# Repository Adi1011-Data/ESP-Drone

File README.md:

# ESP-Drone (XIAO ESP32-C3)

A 1S brushed micro quad. The Seeed XIAO ESP32-C3 is the flight controller. A custom ESC board holds the MPU6050 and four MOSFET motor channels. You fly from the ESP-Drone phone app over the XIAO’s Wi-Fi. This tree is [Circuit Digest ESP-Drone](https://github.com/Circuit-Digest/ESP-Drone) / Espressif ESP-Drone, retargeted from the ESP32-S3 to the ESP32-C3.

Read this page before soldering, installing tools, or flashing.

## What you are building

```text
1S LiPo  -->  ESC board  -->  four 720 coreless motors
                 |  MPU6050 (gyro + accel)
                 |  four AO3400A low-side FETs
                 |
           XIAO ESP32-C3  -->  Wi-Fi AP  -->  phone app (sticks)
                              HTTP :80     -->  laptop (PID page)
                              USB-C        -->  attitude viewer
```

The phone never closes the attitude loop. The chip reads the MPU6050, runs cascaded PID at 500 Hz, and mixes the four motors. If stick packets stop, throttle goes to zero.

This board has no barometer, magnetometer, or optical flow. Stabilize / manual flight only. Height-hold and position-hold need extra sensors that are not fitted.

## Simulation links

The local pages are served by this PC, not by the ESP. They open with the board off. From `simulation/`, start the server and leave that window open. Closing it stops port 8765, and the browser cannot open the sites.

```powershell
.\serve.ps1
```

| Tool | Local (ESP can be off) | On the drone Wi-Fi |
| --- | --- | --- |
| Landing page | http://127.0.0.1:8765/ | — |
| Attitude viewer | http://127.0.0.1:8765/viewer/ | USB or BLE from that page |
| PID tuner | http://127.0.0.1:8765/pid/ | http://192.168.43.42/ |

http://192.168.43.42/ is the ESP. It opens only when the board is on and the laptop has joined its Wi-Fi.

- **Attitude viewer:** props off. Close `idf.py monitor`. Chrome or Edge. Connect USB (or BLE) and tilt the board. The on-screen quad copies the MPU6050.
- **PID tuner:** phone stays on `ESP-DRONE_…` for sticks (UDP **2390**). Laptop joins the same AP. Open the PID link (HTTP **80**). Do not point a second CRTP client at 2390.

More detail: [simulation/README.md](simulation/README.md).

## Architecture

```text
Phone app  --UDP 2390 CRTP-->  Wi-Fi AP (192.168.43.42)
Laptop     --HTTP 80------->  same AP, PID dashboard
USB-C      --ATT,w,x,y,z-->  attitude viewer

Stick angles --> Angle PID --> desired rates --> Rate PID --> mixer --> MOT1..4
                 (outer)                        (inner, gyro)
```

| Piece | What it does |
| --- | --- |
| XIAO ESP32-C3 | Wi-Fi AP, USB Serial/JTAG, PID, PWM to the FETs |
| MPU6050 | Gyro and accelerometer on I2C `0x68` |
| AO3400A × 4 | One low-side switch per brushed motor |
| SS14 × 4 | Flyback diode on each motor |
| ESP-Drone 0.7.3 | Stick input over CRTP |
| PID page | Live Kp/Ki/Kd; Save writes NVS |

Factory PID: [Firmware/main/include/board/pid_config.h](Firmware/main/include/board/pid_config.h). Pins and Wi-Fi: [Firmware/main/include/board/drone_config.h](Firmware/main/include/board/drone_config.h).

Tune **Rate** (inner) until it is calm, then **Angle** (outer). Rate is “don’t wobble.” Angle is “follow the stick.”

## Downloads and tools (do this before flashing)

Work on Windows. Scripts and paths in this repo assume the tools live on **E:** under `Drone-ESC\downloads`. Anaconda Python must not be the `python` that ESP-IDF finds.

1. **ESP-IDF 5.0.7 offline installer** (~0.96 GB)  
   Put `esp-idf-tools-setup-offline-5.0.7.exe` in `downloads/`.  
   Get it from Espressif’s IDF installer releases: [idf-installer](https://github.com/espressif/idf-installer/releases) (offline 5.0.7).

2. **Install onto this drive** (not `C:\Espressif`):

   ```powershell
   cd E:\Drone-ESC\downloads
   .\install-esp-idf-5.0.7.ps1
   ```

   In the installer: keep PowerShell selected, select the **ESP32-C3** target. Tools land in `downloads\Espressif`. The IDF tree is `downloads\Espressif\frameworks\esp-idf-v5.0.7`. The Python venv is `downloads\Espressif\python_env\idf5.0_py3.11_env`.

3. **Phone app** — [ESP-Drone 0.7.3 for Android](https://www.pgyer.com/a27L). Do not change drone IP `192.168.43.42` or UDP port `2390`.

4. **Browser** — Chrome or Edge for the attitude viewer (Web Serial / Web Bluetooth).

5. **Python 3** — only needed for `simulation\serve.ps1` (`python -m http.server`). The IDF venv is enough if it is on PATH.

6. **KiCad 10** — only if you will edit the PCB.

You do not need Node, Docker, or a second copy of ESP-IDF.

## Build and flash

From the repo root, in an ESP-IDF 5.0.7 shell (see the installer notes above):

```powershell
cd Firmware
idf.py set-target esp32c3
idf.py build
```

The image is `Firmware\build\ESPDrone.bin`. `idf.py flash` does not work on this XIAO. Flash with esptool and `usb_reset`, as in [Firmware/FLASHING.md](Firmware/FLASHING.md). Unplug the battery if props are on.

## Bring-up order (props off)

1. 3.3 V present, XIAO seated the right way around.
2. Flash, then USB serial: MPU6050 OK, AP up.
3. Attitude viewer: tilt matches the on-screen quad. Invert an axis in the page if needed; flip `DRONE_GYRO_*_SIGN` / `DRONE_ACC_*_SIGN` in firmware if the board is mechanically reversed.
4. One motor at a time, no props: each corner spins the right way. Swap that motor’s two leads if it is backward. If a corner climbs in a hover, that mixer channel is wrong — see comments in `drone_config.h`.
5. Phone joins `ESP-DRONE_<MAC>`, password `12345678`, app Connect. Throttle at zero, then a blip. Killing the app or leaving Wi-Fi must stop the motors.
6. Props on only after that. First hover in a soft, open space.
7. PID: laptop on the same AP, open http://192.168.43.42/ . Tune Rate, then Angle. **Save** to keep the tune across reboot.

## Fly

1. Power the drone and wait until it is sitting level.
2. Phone: Wi-Fi `ESP-DRONE_<MAC>`, password `12345678`.
3. ESP-Drone app → Connect. Sticks go to `192.168.43.42:2390`.

SSID prefix and password are in `drone_config.h`. Do not change the IP or UDP port; the 0.7.3 app expects them.

## Repo map

| Path | Contents |
| --- | --- |
| [Firmware](Firmware) | ESP-IDF 5.0.7 app |
| [Firmware/FLASHING.md](Firmware/FLASHING.md) | How this XIAO is actually programmed |
| [simulation](simulation) | Attitude viewer and PID tuner |
| [hardware/PCB/ESC](hardware/PCB/ESC) | Schematic, PCB, Gerbers, BOM |

Upstream video: [youtu.be/V_mZsiZcy7s](https://youtu.be/V_mZsiZcy7s). This board is C3, not S3.

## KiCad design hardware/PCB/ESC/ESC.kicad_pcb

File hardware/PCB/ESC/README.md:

# ESC-ESP32C3

A small brushed-motor ESC and flight-controller board for a drone built around a Seeed Studio XIAO ESP32-C3. The XIAO is the flight controller. An MPU6050 on the board supplies the accelerometer and gyroscope. Four 720 coreless motors are switched by AO3400A MOSFETs. The drone is flown from the ESP-Drone phone app over the XIAO's Wi-Fi.

## Board

Motor side. The XIAO plugs into headers J1 and J3. M1–M4 are the motor pads.

Sensor side. U1 is the MPU6050. The battery connects at the BAT pads.

## Parts

| Part | Role |
| --- | --- |
| Seeed Studio XIAO ESP32-C3 | Flight controller. Plugs into J1 and J3. |
| MPU6050 (U1) | 6-axis gyro and accelerometer, I2C address 0x68 (AD0 held low). |
| 720 coreless motor × 4 | Brushed motors on M1, M2, M3, and M4. |
| AO3400A × 4 | Low-side MOSFET for each motor. |
| Schottky diode × 4 | Flyback diode across each motor (SOD-323). |
| ESP-Drone app | Phone app used to control the drone. |

## XIAO pins

Seat the XIAO with the USB end toward the 5V / D0 end of the headers (J3 pin 1 is 5V, J1 pin 1 is D0).

| XIAO pin | GPIO | Function |
| --- | --- | --- |
| D0 | GPIO2 | Motor 1 gate (MOT1) |
| D3 | GPIO5 | Motor 2 gate (MOT2) |
| D9 | GPIO9 | Motor 3 gate (MOT3) |
| D10 | GPIO10 | Motor 4 gate (MOT4) |
| D4 | GPIO6 | MPU6050 SDA |
| D5 | GPIO7 | MPU6050 SCL |
| D7 | GPIO20 | MPU6050 interrupt |
| D2 | GPIO4 | Battery voltage sense |
| 3V3 | — | Sensor and gate pull-ups |
| GND | — | Common ground |

D9 is a boot strap pin. Its gate pull-down must leave the pin high enough at reset for the XIAO to start normally. Holding D9 low during reset puts the module into download mode.

D6 (GPIO21) is left free. It is the serial transmit pin and toggles while the chip boots.

## Assembly

1. Solder the MPU6050, MOSFETs, diodes, and passives.
2. Plug the XIAO ESP32-C3 into J1 and J3. Do not reverse it: 5V and D0 share one end of the module.
3. Solder one 720 coreless motor to each of M1–M4. The motor positive lead goes to the BAT+ pad of that pair.
4. Connect the flight battery at the BAT pads.
5. Power the XIAO, join its Wi-Fi from the ESP-Drone app, and arm the motors only after the propellers are clear.

## Design files

Open `ESC.kicad_pro` in KiCad 10.

| Path | Contents |
| --- | --- |
| `ESC.kicad_sch` | Schematic |
| `ESC.kicad_pcb` | PCB layout |
| `libraries/` | XIAO ESP32-C3 and MPU6050 symbols and footprints |
| `GERBER/` | Fabrication Gerbers and drill files |
| `ESC-BOM.csv` | Bill of materials |
| `ESC-all-pos.csv` | Pick-and-place positions |
| `ESC-ESP32.step` | 3D model of the board |

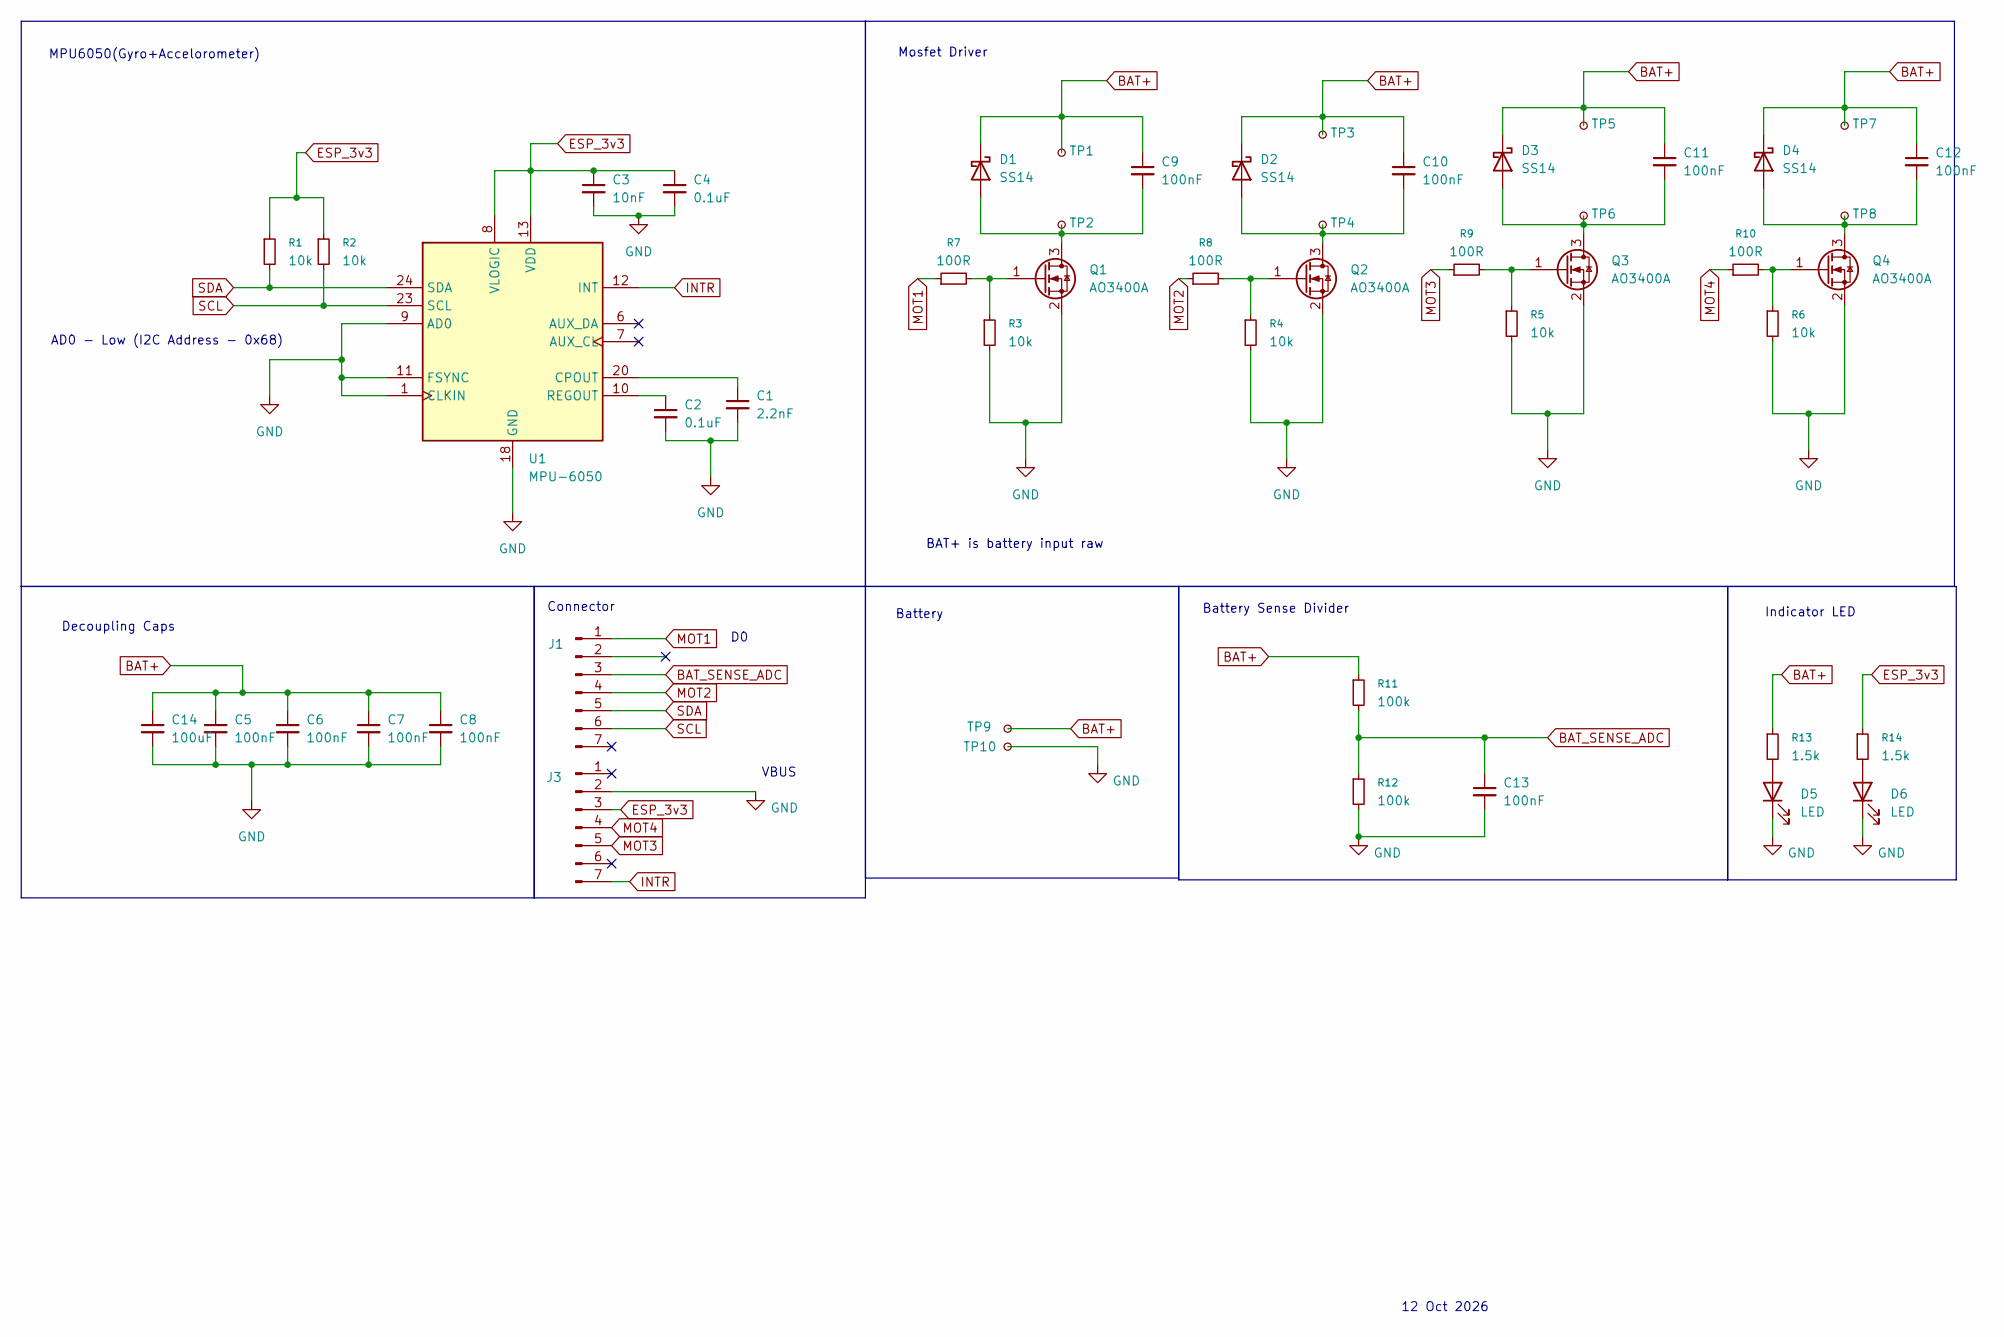
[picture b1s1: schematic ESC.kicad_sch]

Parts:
C1: 2.2nF; C_0402_1005Metric_Pad0.74x0.62mm_HandSolder
C2, C4: 0.1uF; C_0402_1005Metric_Pad0.74x0.62mm_HandSolder
C3: 10nF; C_0402_1005Metric_Pad0.74x0.62mm_HandSolder
C5, C6, C7, C8, C9, C10, C11, C12, C13: 100nF; C_0402_1005Metric_Pad0.74x0.62mm_HandSolder
C14: 100uF; C_0402_1005Metric_Pad0.74x0.62mm_HandSolder
D1, D2, D3, D4: SS14; D_SOD-323_HandSoldering
D5, D6: LED; LED_0402_1005Metric_Pad0.77x0.64mm_HandSolder
J1, J3: Conn_01x07_Pin; PinHeader_1x07_P2.54mm_Vertical
Q1, Q2, Q3, Q4: AO3400A; SOT-23
R1, R2, R3, R4, R5, R6: 10k; R_0402_1005Metric_Pad0.72x0.64mm_HandSolder
R7, R8, R9, R10: 100R; R_0402_1005Metric_Pad0.72x0.64mm_HandSolder
R11, R12: 100k; R_0402_1005Metric_Pad0.72x0.64mm_HandSolder
R13, R14: 1.5k; R_0402_1005Metric_Pad0.72x0.64mm_HandSolder
TP1, TP3, TP5, TP7, TP9: TestPoint_Small; TestPoint_Pad_1.0x1.0mm
TP2, TP4, TP6, TP8, TP10: TestPoint_Small; TestPoint_Pad_D1.0mm
U1: MPU-6050; InvenSense_QFN-24_4x4mm_P0.5mm

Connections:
BAT+: C5.1, C6.1, C7.1, C8.1, C9.1, C10.1, C11.1, C12.1, C14.1, D1.1 (K), D2.1 (K), D3.1 (K), D4.1 (K), R11.1, R13.1, TP1.1 (1_1), TP3.1 (1_1), TP5.1 (1_1), TP7.1 (1_1), TP9.1 (1_1)
BAT_SENSE_ADC: C13.1, J1.3, R11.2, R12.1
ESP_3v3: C3.1, C4.1, J3.3, R1.1, R2.1, R14.1, U1.8 (VLOGIC), U1.13 (VDD)
GND: C1.2, C2.2, C3.2, C4.2, C5.2, C6.2, C7.2, C8.2, C13.2, C14.2, D5.1 (K), D6.1 (K), J3.2, Q1.2 (S), Q2.2 (S), Q3.2 (S), Q4.2 (S), R3.2, R4.2, R5.2, R6.2, R12.2, TP10.1 (1_1), U1.1 (CLKIN), U1.9 (AD0), U1.11 (FSYNC), U1.18 (GND)
INTR: J3.7, U1.12 (INT)
MOT1: J1.1, R7.1
MOT2: J1.4, R8.1
MOT3: J3.5, R9.1
MOT4: J3.4, R10.1
unnamed: C9.2, D1.2 (A), Q1.3 (D), TP2.1 (1_1)
unnamed: C10.2, D2.2 (A), Q2.3 (D), TP4.1 (1_1)
unnamed: C11.2, D3.2 (A), Q3.3 (D), TP6.1 (1_1)
unnamed: C12.2, D4.2 (A), Q4.3 (D), TP8.1 (1_1)
unnamed: D5.2 (A), R13.2
unnamed: D6.2 (A), R14.2
unnamed: Q1.1 (G), R3.1, R7.2
unnamed: Q2.1 (G), R4.1, R8.2
unnamed: Q3.1 (G), R5.1, R9.2
unnamed: Q4.1 (G), R6.1, R10.2
unnamed: C1.1, U1.20 (CPOUT)
unnamed: C2.1, U1.10 (REGOUT)
SCL: J1.6, R2.2, U1.23 (SCL)
SDA: J1.5, R1.2, U1.24 (SDA)

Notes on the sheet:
BAT+ is battery input raw
Battery Sense Divider
12 Oct 2026
Decoupling Caps
Indicator LED
MPU6050(Gyro+Accelorometer)
Mosfet Driver
Battery
AD0 - Low (I2C Address - 0x68)
Connector
VBUS

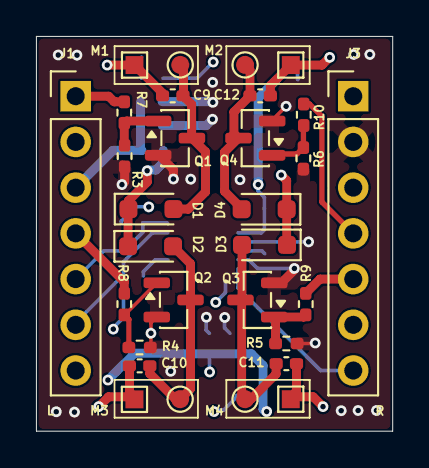
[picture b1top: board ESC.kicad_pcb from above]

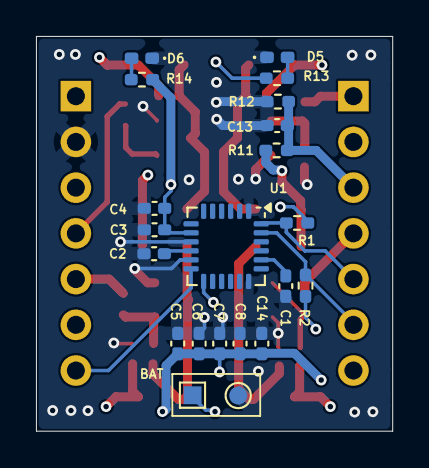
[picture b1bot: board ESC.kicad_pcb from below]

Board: 4 copper layers, 19.8 x 21.9 mm, 51 parts (21 on the bottom side), 23 nets.

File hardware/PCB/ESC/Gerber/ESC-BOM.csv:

"Id";"Designator";"Footprint";"Quantity";"Designation";"Supplier and ref";
1;"C1";"C_0402_1005Metric_Pad0.74x0.62mm_HandSolder";1;"2.2nF";;;
2;"C2, C4";"C_0402_1005Metric_Pad0.74x0.62mm_HandSolder";2;"0.1uF";;;
3;"C3";"C_0402_1005Metric_Pad0.74x0.62mm_HandSolder";1;"10nF";;;
4;"C5, C6, C7, C8, C9, C10, C11, C12, C13";"C_0402_1005Metric_Pad0.74x0.62mm_HandSolder";9;"100nF";;;
5;"C14";"C_0402_1005Metric_Pad0.74x0.62mm_HandSolder";1;"100uF";;;
6;"D1, D2, D3, D4";"D_SOD-323_HandSoldering";4;"SS14";;;
7;"D5, D6";"LED_0402_1005Metric_Pad0.77x0.64mm_HandSolder";2;"LED";;;
8;"J1, J3";"PinHeader_1x07_P2.54mm_Vertical";2;"Conn_01x07_Pin";;;
9;"Q1, Q2, Q3, Q4";"SOT-23";4;"AO3400A";;;
10;"R1, R2, R3, R4, R5, R6";"R_0402_1005Metric_Pad0.72x0.64mm_HandSolder";6;"10k";;;
11;"R7, R8, R9, R10";"R_0402_1005Metric_Pad0.72x0.64mm_HandSolder";4;"100R";;;
12;"R11, R12";"R_0402_1005Metric_Pad0.72x0.64mm_HandSolder";2;"100k";;;
13;"R13, R14";"R_0402_1005Metric_Pad0.72x0.64mm_HandSolder";2;"1.5k";;;
14;"TP1, TP3, TP5, TP7, TP9";"TestPoint_Pad_1.0x1.0mm";5;"TestPoint_Small";;;
15;"TP2, TP4, TP6, TP8, TP10";"TestPoint_Pad_D1.0mm";5;"TestPoint_Small";;;
16;"U1";"InvenSense_QFN-24_4x4mm_P0.5mm";1;"MPU-6050";;;

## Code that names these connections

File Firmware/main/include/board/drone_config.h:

/**
 * XIAO ESP32-C3 flight settings for this ESC board.
 *
 * Change values here, then rebuild and flash. This file replaces the
 * matching menuconfig values, so you do not have to open menuconfig
 * for pins, battery scale, axis signs, or the Wi-Fi password.
 * Attitude PID factory defaults live in pid_config.h. Live tuning
 * is the HTTP dashboard (simulation/pid); it does not need a reflash.
 *
 * Props off until each motor spins the right way on the bench.
 */
#ifndef DRONE_CONFIG_H_
#define DRONE_CONFIG_H_

/* -------------------------------------------------------------------------- */
/* MOSFET gates. Low-side AO3400A, one GPIO per motor.                       */
/* XIAO pin -> GPIO. These match the ESC schematic.                          */
/*                                                                            */
/*   MOT1  D0   GPIO2   mixer M1, front-left                                  */
/*   MOT2  D10  GPIO10  mixer M2, front-right                                 */
/*   MOT3  D1   GPIO3   mixer M3, rear-right                                  */
/*   MOT4  D3   GPIO5   mixer M4, rear-left                                   */
/*                                                                            */
/* D9 / GPIO9 is the XIAO BOOT strap. Leave it unconnected. Holding it low   */
/* at reset enters download mode. Do not use D8 / GPIO8 for a motor either.  */
/* If a corner climbs instead of holding level, swap that motor's GPIO       */
/* with the corner that should have received the correction.                 */
/* -------------------------------------------------------------------------- */
#define DRONE_MOTOR1_GPIO          2
#define DRONE_MOTOR2_GPIO          10
#define DRONE_MOTOR3_GPIO          3
#define DRONE_MOTOR4_GPIO          5

/* LEDC channels 0-3. ESP32-C3 has six channels; 6 and 7 do not exist. */
#define DRONE_MOTOR_PWM_HZ         20000

/* Minimum command while armed, 0..65535. 0 keeps the props stopped at idle. */
#define DRONE_IDLE_THRUST          0

/* -------------------------------------------------------------------------- */
/* MPU6050. AD0 is tied low, so the address is 0x68.                         */
/*   SDA  D4  GPIO6                                                          */
/*   SCL  D5  GPIO7                                                          */
/*   INT  D7  GPIO20                                                         */
/* Signs are +1 or -1. Flip a sign if that axis is reversed on the bench.   */
/* -------------------------------------------------------------------------- */
#define DRONE_I2C_SDA_GPIO         6
#define DRONE_I2C_SCL_GPIO         7
#define DRONE_MPU_INT_GPIO         20

#define DRONE_GYRO_X_SIGN          (-1)
#define DRONE_GYRO_Y_SIGN          (1)
#define DRONE_GYRO_Z_SIGN          (1)
#define DRONE_ACC_X_SIGN           (-1)
#define DRONE_ACC_Y_SIGN           (1)
#define DRONE_ACC_Z_SIGN           (1)

/* Attitude lines on the USB-C serial port, for simulation/viewer.
 * Format: ATT,<w>,<x>,<y>,<z>
 * 0 turns the stream off. Close idf.py monitor before the viewer
 * opens this same COM port. */
#define DRONE_USB_ATTITUDE_HZ      100

/* Level trim in centidegrees. 90 means 0.90 degree. */
#define DRONE_PITCH_CALIB_CENTIDEG 0
#define DRONE_ROLL_CALIB_CENTIDEG  0

/* -------------------------------------------------------------------------- */
/* Battery. R11 and R12 are both 100k, so the ADC sees half the cell.        */
/* Sense pin is D2 / GPIO4, which is ADC1 channel 4 on the ESP32-C3.         */
/* -------------------------------------------------------------------------- */
#define DRONE_VBAT_GPIO            4
#define DRONE_VBAT_ADC_CHANNEL     4
#define DRONE_BATTERY_DIVIDER      2.0f

/* 255 disables a LED. This board has no status LEDs on free GPIOs. */
#define DRONE_LED_RED_GPIO         255
#define DRONE_LED_GREEN_GPIO       255
#define DRONE_LED_BLUE_GPIO        255

/* No buzzer is fitted. Set to 1 only after two free GPIOs are wired. */
#define DRONE_BUZZER_ENABLE        0

/* No optical-flow deck. Negative pins keep SPI off the motor gates. */
#define DRONE_SPI_MISO             (-1)
#define DRONE_SPI_MOSI             (-1)
#define DRONE_SPI_CLK              (-1)
#define DRONE_SPI_CS               (-1)

/* -------------------------------------------------------------------------- */
/* ESP-Drone Android app 0.7.3 (https://www.pgyer.com/a27L).                  */
/* The phone joins "<prefix>_<MAC>" with the password below, then the app    */
/* sends CRTP to the address and UDP port. Those two must stay as written.   */
/* -------------------------------------------------------------------------- */
#define DRONE_WIFI_SSID_PREFIX     "ESP-DRONE"
#define DRONE_WIFI_PASSWORD        "12345678"
#define DRONE_WIFI_IP              "192.168.43.42"
#define DRONE_UDP_PORT             2390

/* PID dashboard HTTP. Must not share UDP 2390 with the phone app. */
#define DRONE_PID_HTTP_PORT        80

/* Apply the values above on top of menuconfig / sdkconfig.h. */
#ifdef CONFIG_MOTOR01_PIN
#undef CONFIG_MOTOR01_PIN
#endif
#define CONFIG_MOTOR01_PIN DRONE_MOTOR1_GPIO

#ifdef CONFIG_MOTOR02_PIN
#undef CONFIG_MOTOR02_PIN
#endif
#define CONFIG_MOTOR02_PIN DRONE_MOTOR2_GPIO

#ifdef CONFIG_MOTOR03_PIN
#undef CONFIG_MOTOR03_PIN
#endif
#define CONFIG_MOTOR03_PIN DRONE_MOTOR3_GPIO

#ifdef CONFIG_MOTOR04_PIN
#undef CONFIG_MOTOR04_PIN
#endif
#define CONFIG_MOTOR04_PIN DRONE_MOTOR4_GPIO

#ifdef CONFIG_I2C0_PIN_SDA
#undef CONFIG_I2C0_PIN_SDA
#endif
#define CONFIG_I2C0_PIN_SDA DRONE_I2C_SDA_GPIO

#ifdef CONFIG_I2C0_PIN_SCL
#undef CONFIG_I2C0_PIN_SCL
#endif
#define CONFIG_I2C0_PIN_SCL DRONE_I2C_SCL_GPIO

#ifdef CONFIG_MPU_PIN_INT
#undef CONFIG_MPU_PIN_INT
#endif
#define CONFIG_MPU_PIN_INT DRONE_MPU_INT_GPIO

#ifdef CONFIG_ADC1_PIN
#undef CONFIG_ADC1_PIN
#endif
#define CONFIG_ADC1_PIN DRONE_VBAT_GPIO

#ifdef CONFIG_LED_PIN_RED
#undef CONFIG_LED_PIN_RED
#endif
#define CONFIG_LED_PIN_RED DRONE_LED_RED_GPIO

#ifdef CONFIG_LED_PIN_GREEN
#undef CONFIG_LED_PIN_GREEN
#endif
#define CONFIG_LED_PIN_GREEN DRONE_LED_GREEN_GPIO

#ifdef CONFIG_LED_PIN_BLUE
#undef CONFIG_LED_PIN_BLUE
#endif
#define CONFIG_LED_PIN_BLUE DRONE_LED_BLUE_GPIO

#ifdef CONFIG_PITCH_CALIB
#undef CONFIG_PITCH_CALIB
#endif
#define CONFIG_PITCH_CALIB DRONE_PITCH_CALIB_CENTIDEG

#ifdef CONFIG_ROLL_CALIB
#undef CONFIG_ROLL_CALIB
#endif
#define CONFIG_ROLL_CALIB DRONE_ROLL_CALIB_CENTIDEG

#ifdef CONFIG_SPI_PIN_MISO
#undef CONFIG_SPI_PIN_MISO
#endif
#define CONFIG_SPI_PIN_MISO DRONE_SPI_MISO

#ifdef CONFIG_SPI_PIN_MOSI
#undef CONFIG_SPI_PIN_MOSI
#endif
#define CONFIG_SPI_PIN_MOSI DRONE_SPI_MOSI

#ifdef CONFIG_SPI_PIN_CLK
#undef CONFIG_SPI_PIN_CLK
#endif
#define CONFIG_SPI_PIN_CLK DRONE_SPI_CLK

#ifdef CONFIG_SPI_PIN_CS0
#undef CONFIG_SPI_PIN_CS0
#endif
#define CONFIG_SPI_PIN_CS0 DRONE_SPI_CS

#if !DRONE_BUZZER_ENABLE
#undef CONFIG_BUZZER_ON
#endif

#ifndef DEFAULT_IDLE_THRUST
#define DEFAULT_IDLE_THRUST DRONE_IDLE_THRUST
#endif

#endif /* DRONE_CONFIG_H_ */
